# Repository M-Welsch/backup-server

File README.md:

# Backup Server (BaSe)

Your Home NAS requires you to make backups from time to time. Since you have better things to do, these will likely get forgotten or done irregulary. The Backup-Server aims on helping you out. It backs up your data on schedule and undocks the backup medium when the backup is done. This offers an unique way of data protection.

## Introduction (longer)

Like many other people (*cough* nerds) I have a home NAS that serves nextcloud and some other funny stuff. Thanks to a terrific community it became quite easy to setup such a thing. Many, many thanks to you all!
However, hosting my own server came with a serious disadvantage. I had to take care of the backups myself.

I built Backup Server to overcome this issue. It sleeps and therefore consumes very, very little current most of the times, wakes up when a backup is scheduled, docks to a hard drive, copys all the data from the nas, undocks and goes back to sleep.

## Implementation

The current verion is built around a banana pi mk1. It connects to the hard drive via a motor-driven pluggable sata-connection, which is the core of the whole thing. This way, the harddrive is only connected to anything if needed.

```mermaid
graph LR
A(Power Up)-->B(Dock external HDD)-->C(Conduct Backup)-->D(Schedule Next Backup)-->E(Undock external HDD)-->F(Schedule next Backup)-->G(Power Down)
```

## Outlook

the next hardware version shall be more flexible compared to our custom fit to the banana pi.

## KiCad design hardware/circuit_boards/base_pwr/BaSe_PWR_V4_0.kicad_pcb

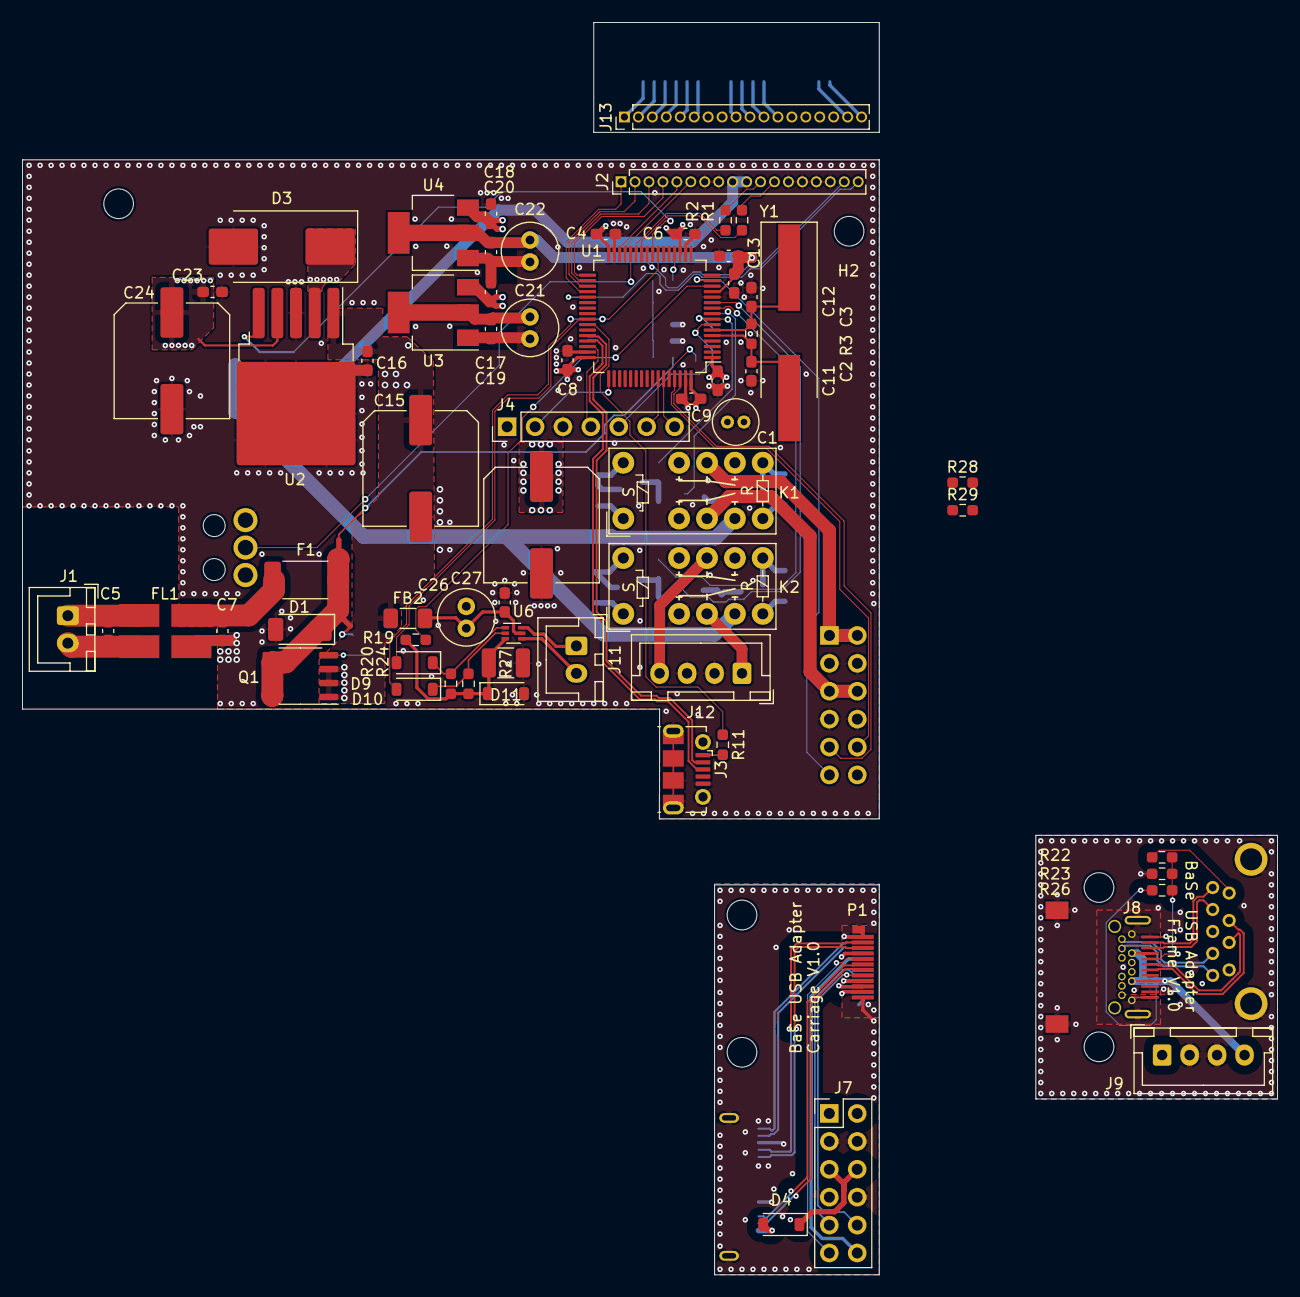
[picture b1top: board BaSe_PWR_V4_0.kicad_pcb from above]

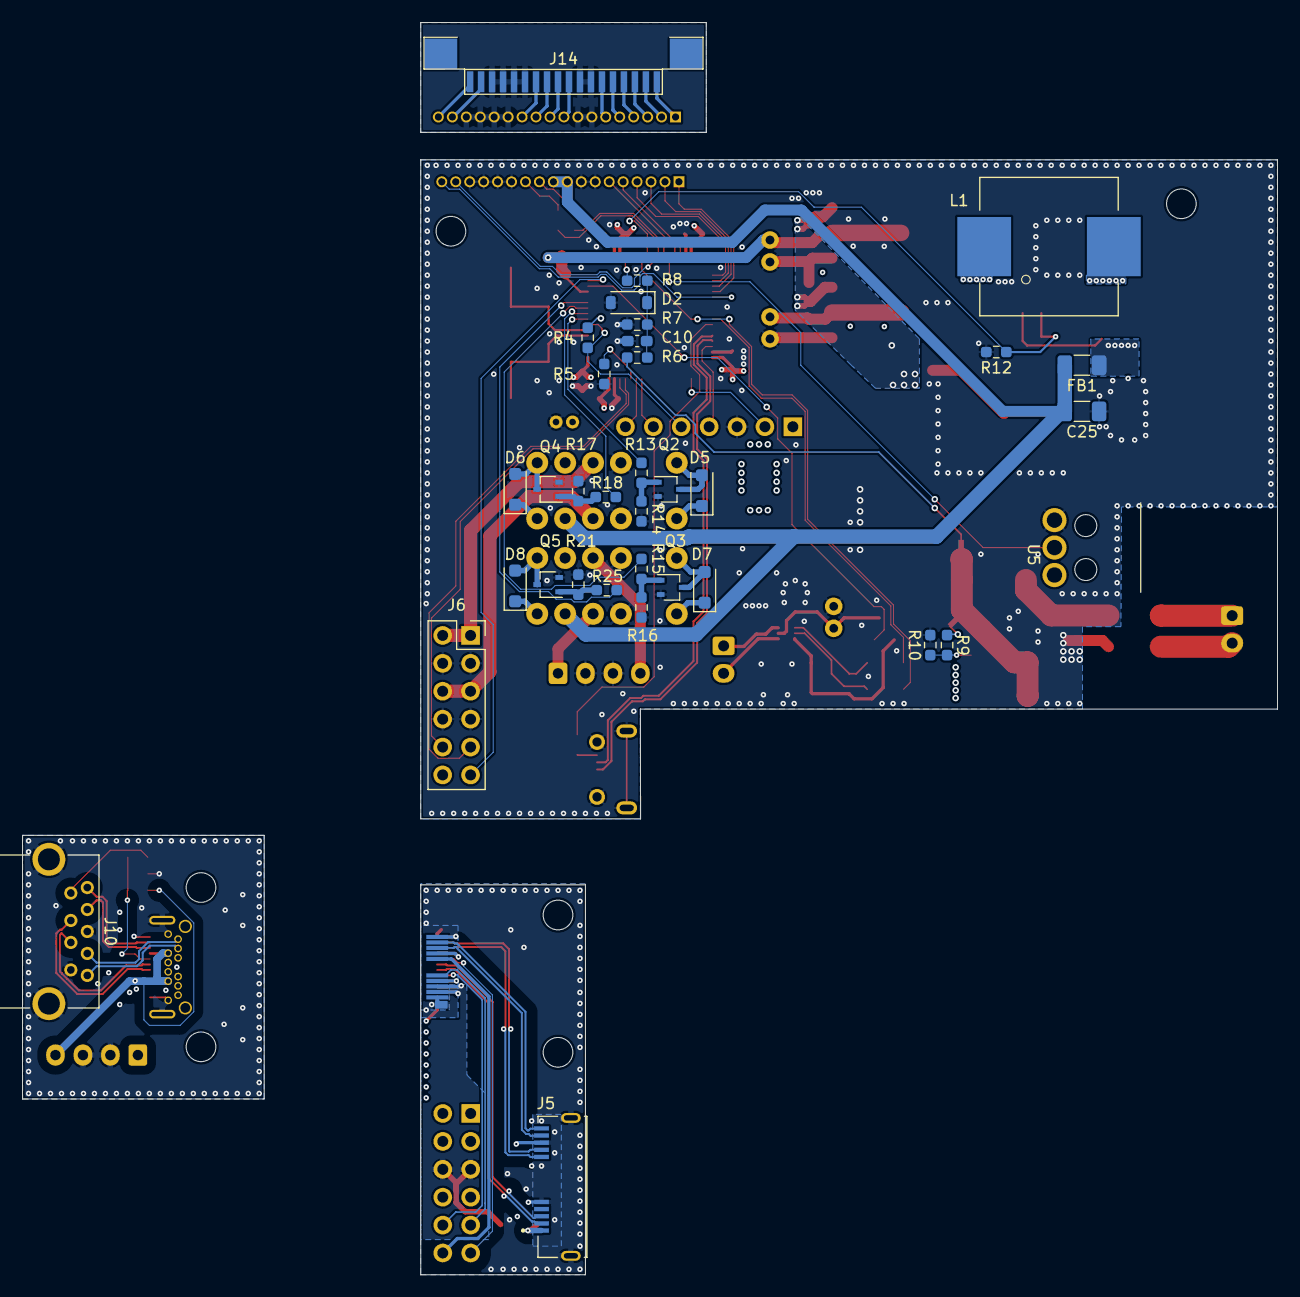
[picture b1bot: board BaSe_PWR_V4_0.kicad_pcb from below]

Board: 4 copper layers, 114.2 x 114.0 mm, 109 parts (34 on the bottom side), 106 nets.

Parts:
C1: 4.7µF; C_Radial_D4.0mm_H7.0mm_P1.50mm
C2, C3: 20pF; C_0603_1608Metric_Pad1.08x0.95mm_HandSolder
C4, C6, C8, C9, C10, C11, C16, C17, C18, C19, C20, C23, C27: 100nF; C_0603_1608Metric_Pad1.08x0.95mm_HandSolder
C5, C7: C_0603_1608Metric_Pad1.08x0.95mm_HandSolder
C12: 10nF; C_0603_1608Metric_Pad1.08x0.95mm_HandSolder
C13: 1µF; C_0603_1608Metric_Pad1.08x0.95mm_HandSolder
C14, C15, C24: 220µF; C_Elec_10x10.2
C21, C22, C26: 22µF; C_Radial_D5.0mm_H11.0mm_P2.00mm
C25: 10µF; C_1206_3216Metric_Pad1.33x1.80mm_HandSolder
D1: 824501121; D_SOD-128
D2, D9, D10: SD103CW-E3-08; D_SOD-123
D3: SK34-TP; D_SMC_Handsoldering
D4: SK64L-TPMSCT-ND; D_SOD-123
D5, D6, D7, D8: 1N4148WRHGCT-ND; D_SOD-123F
D11: 2.5V; D_SOD-123
F1: Fuse_2512_6332Metric_Pad1.52x3.35mm_HandSolder
FB1, FB2: FerriteBead; C_1206_3216Metric_Pad1.33x1.80mm_HandSolder
FL1: CMC_Laird_CM2021Y330R-10
H1, H2, H3, H4, H5, H6: MountingHole; MountingHole_2.7mm_M2.5_DIN965
J1: 12VDC In; JST_XH_B2B-XH-A_1x02_P2.50mm_Vertical
J2: HRS-1B-16-GA; PinHeader_1x18_P1.27mm_Vertical
J3: USB_B_Micro; USB_Micro-B_Molex-105017-0001
J4: Conn_01x07_Pin; PinHeader_1x07_P2.54mm_Vertical
J5: USB3_B_Micro; conn_usb3bmicro_GSB343K331HR
J6: Conn_02x06_Odd_Even; PinSocket_2x06_P2.54mm_Vertical
J7: Conn_02x06_Odd_Even; PinHeader_2x06_P2.54mm_Vertical
J8: USB_C_Receptacle; conn_usbc_socket_RAHPCUC31AU1TR
J9, J12: Conn_01x04_Socket; JST_XH_B4B-XH-A_1x04_P2.50mm_Vertical
J10: USB3_A; STEWARD_USB3_A_SS-52000-001
J11: MOTOR; JST_XH_B2B-XH-A_1x02_P2.50mm_Vertical
J13: HPH1-A-16-UA; PinHeader_1x18_P1.27mm_Vertical
J14: molex_fcc_05220
K1, K2: Kemet_EC2-12TNU
L1: 47µH; L_Wuerth_WE-PD-Typ-LS_Handsoldering
NT1, NT2: NetTie_2; NetTie-2_SMD_Pad0.5mm
P1: USB_C_Plug; Molex_USBC_Plug_1054440011
Q1: AOSP21321; SO-8_3.9x4.9mm_P1.27mm
Q2, Q3, Q4, Q5: BSS214NW; SOT-323_SC-70
R1, R2, R8, R10: 100; R_0603_1608Metric_Pad0.98x0.95mm_HandSolder
R3: R; R_0603_1608Metric_Pad0.98x0.95mm_HandSolder
R4, R5, R11, R20, R24, R28: 10k; R_0603_1608Metric_Pad0.98x0.95mm_HandSolder
R6, R9: 100k; R_0603_1608Metric_Pad0.98x0.95mm_HandSolder
R7: 24,9k; R_0603_1608Metric_Pad0.98x0.95mm_HandSolder
R12, R14, R16, R17, R21: 47k; R_0603_1608Metric_Pad0.98x0.95mm_HandSolder
R13, R15, R18, R19, R25: 1k; R_0603_1608Metric_Pad0.98x0.95mm_HandSolder
R22: 13,3k; R_0603_1608Metric_Pad0.98x0.95mm_HandSolder
R23: 3,16k; R_0603_1608Metric_Pad0.98x0.95mm_HandSolder
R26: 15,8k; R_0603_1608Metric_Pad0.98x0.95mm_HandSolder
R27: R; R_1210_3225Metric_Pad1.30x2.65mm_HandSolder
R29: 8,87k; R_0603_1608Metric_Pad0.98x0.95mm_HandSolder
U1: STM32F070RBTx; LQFP-64_10x10mm_P0.5mm
U2: LM2596S-5; TO-263-5_TabPin3
U3, U4: AMS1117-3.3; SOT-223-3_TabPin2
U5: TS0101F020V4
U6: DRV8220; SOT-563
Y1: 8MHz; Crystal_SMD_HC49-SD_HandSoldering

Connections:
+3.3VA: C12.1, C13.1, C20.1, C22.1, U1.13 (VDDA), U4.2 (VO)
+3V3_STBY: C1.1, C4.1, C6.1, C8.1, C9.1, C11.1, C19.1, C21.1, J4.1, J6.12, R4.2, R28.1, R29.2, U1.1 (VDD), U1.19 (VDD), U1.32 (VDD), U1.48 (VDD), U1.64 (VDD), U3.2 (VO)
+5V: C25.2, FB1.2, J2.9, J2.10, K1.5, K2.5
+5VA: J8.A10 (RX2-), J8.A11 (RX2+), J8.B2 (TX2+), J8.B3 (TX2-), J9.1, J10.1 (VBUS), R22.1
+12V: C14.1, C15.1, C16.2, C17.1, C18.1, D5.1 (K), D6.1 (K), D7.1 (K), D8.1 (K), FB2.1, K1.1, K1.6, K1.8, K2.1, K2.6, K2.8, Q1.1 (S), Q1.2 (S), Q1.3 (S), U2.1 (VIN), U3.3 (VI), U4.3 (VI)
+12VA: J8.A4 (VBUS), J8.A9 (VBUS), J8.B4 (VBUS), J8.B9 (VBUS), J9.4, R26.1
/12v_motor: C26.1, C27.1, FB2.2, U6.5 (VM)
/12vin_meas: R8.2, U1.20 (PA4)
/+5V_HDD: J6.5, J6.6, K1.4
/+5V_HDD_: D4.1 (K), J7.5, J7.6, P1.A10 (RX2-), P1.A11 (RX2+), P1.B2 (TX2+), P1.B3 (TX2-)
/+5V_sbu: J12.1, K2.4
/+5v_out: C23.2, C24.1, FB1.1, L1.2, U2.4 (FB)
/+12V_HDD: J6.1, J6.2, K1.9
/+12V_HDD_: J7.1, J7.2, P1.A4 (VBUS), P1.A9 (VBUS), P1.B4 (VBUS), P1.B9 (VBUS)
/+12V_sbu: J12.4, K2.9
/DC_IN+: C5.2, FL1.1, J1.1
/DC_IN-: C5.1, FL1.2, J1.2
/DC_prefuse: C7.1, F1.2, FL1.4
/DC_preprot: D1.1 (A1), F1.1, NT1.2, NT2.2, Q1.5 (D), Q1.6 (D), Q1.7 (D), Q1.8 (D)
/Dis_DB4: J2.4, U1.33 (PB12)
/Dis_DB5: J2.3, U1.34 (PB13)
/Dis_DB6: J2.2, U1.35 (PB14)
/Dis_DB7: J2.1, U1.36 (PB15)
/Dis_E: J2.5, U1.30 (PB11)
/Dis_PWM: J2.12, R1.2
/Dis_RS: J2.6, U1.29 (PB10)
/GND_HMI: J13.7, J13.8, J13.13, J13.14, J13.15, J13.16, J14.7, J14.8, J14.13, J14.14, J14.15, J14.16
/LED_HMI: J2.11, R2.2
/SW: D3.1 (K), L1.1, U2.2 (OUT)
/SW_HDD_Off: R18.1, U1.9 (PC1)
/SW_HDD_On: R13.1, U1.8 (PC0)
/Taster_0: J2.17, U1.25 (PC5)
/Taster_1: J2.18, U1.37 (PC6)
/USB_D+: J3.3 (D+), U1.45 (PA12)
/USB_D-: J3.2 (D-), U1.44 (PA11)
/aux_3v3: J7.12, P1.B8 (SBU2)
/aux_i2c_scl: J7.10, P1.A8 (SBU1)
/aux_i2c_sda: J7.9, P1.B5 (VCONN)
/boot0: R5.1, U1.60 (BOOT0)
/hmi_pwm0: R1.1, U1.26 (PB0)
/hmi_pwm1: R2.1, U1.27 (PB1)
/i2c1_scl: J6.10, U1.61 (PB8)
/i2c1_sda: J6.9, U1.62 (PB9)
/imotor: D11.1 (K), R19.2, R20.2, R24.2, R27.1, U6.3 (GND)
/imotor_prot: R19.1, U1.14 (PA0)
/in1: D9.1 (K), R20.1, U6.1 (IN1)
/in1_mcu: D9.2 (A), U1.41 (PA8)
/in2: D10.1 (K), R24.1, U6.2 (IN2)
/in2_mcu: D10.2 (A), U1.23 (PA7)
/l1_rx+: J8.B11 (RX1+), J10.6 (SSRX+)
/l1_rx-: J8.B10 (RX1-), J10.5 (SSRX-)
/l1_tx+: J8.A2 (TX1+), J10.9 (SSTX+)
/l1_tx-: J8.A3 (TX1-), J10.8 (SSTX-)
/lane1_d+: J8.A6 (D+), J10.3 (D+)
/lane1_d-: J8.A7 (D-), J10.2 (D-)
/motor1: J11.1, U6.6 (OUT1)
/motor2: J11.2, U6.4 (OUT2)
/stator_d+: J5.3 (D+), P1.A6 (D+)
/stator_d-: J5.2 (D-), P1.A7 (D-)
/stator_rx+: J5.10 (SSRX+), P1.B11 (RX1+)
/stator_rx-: J5.9 (SSRX-), P1.B10 (RX1-)
/stator_supply_sense: J6.11, R29.1, U1.15 (PA1)
/stator_supply_sense_: J7.11, P1.A5 (CC), R28.2
/stator_tx+: J5.7 (SSTX+), P1.A2 (TX1+)
/stator_tx-: J5.6 (SSTX-), P1.A3 (TX1-)
/supply_sense: J8.A5 (CC1), R22.2, R23.1, R26.2
/sw_sbu_off: R25.1, U1.11 (PC3)
/sw_sbu_on: R15.1, U1.10 (PC2)
/swclk: J4.2, U1.49 (PA14)
/swdio: J4.4, U1.46 (PA13)
/usart1_rx: J4.7, U1.59 (PB7)
/usart1_tx: J4.6, U1.58 (PB6)
/vbus_sense: R11.1, U1.42 (PA9)
/~LM2596S_ON: R12.1, U1.24 (PC4), U2.5 (~ON/OFF)
/~endswitch_undocked: U1.28 (PB2), U5.NO
/~rst: J4.5, R4.1, U1.7 (NRST)
GND: C1.2, C2.1, C3.1, C4.2, C6.2, C7.2, C8.2, C9.2, C10.2, C11.2, C12.2, C13.2, C14.2, C15.2, C16.1, C17.2, C18.2, C19.2, C20.2, C21.2, C22.2, C23.1, C24.2, C25.1, C26.2, C27.2, D1.2 (A2), D2.2 (A), D3.2 (A), D11.2 (A), FL1.3, J2.7, J2.8, J2.13, J2.14, J2.15, J2.16, J3.5 (GND), J3.6 (Shield), J4.3, J6.3, J6.4, J6.7, J6.8, J12.2, J12.3, K1.3, K1.10, K2.3, K2.10, Q2.2 (S), Q3.2 (S), Q4.2 (S), Q5.2 (S), R5.2, R7.1, R10.2, R12.2, R14.1, R16.1, R17.1, R21.1, R27.2, U1.12 (VSSA), U1.18 (VSS), U1.31 (VSS), U1.47 (VSS), U1.63 (VSS), U2.3 (GND), U3.1 (GND), U4.1 (GND), U5.C
GND1: J5.5 (GND), J5.8 (DRAIN), J5.11 (SHIELD), J7.3, J7.4, J7.7, J7.8, P1.A1 (GND), P1.A12 (GND), P1.B1 (GND), P1.B12 (GND), P1.S1 (SHIELD)
GND2: J8.A1 (GND), J8.A12 (GND), J8.B1 (GND), J8.B12 (GND), J8.S1 (SHIELD), J9.2, J9.3, J10.4 (GND), J10.7 (DRAIN), J10.10 (SHIELD), R23.2
unnamed: C10.1, D2.1 (K), R6.1, R7.2, R8.1
unnamed: D4.2 (A), J5.1 (VBUS)
unnamed: D5.2 (A), K1.12, Q2.3 (D)
unnamed: D6.2 (A), K1.7, Q4.3 (D)
unnamed: D7.2 (A), K2.12, Q3.3 (D)
unnamed: D8.2 (A), K2.7, Q5.3 (D)
unnamed: J3.1 (VBUS), R11.2
unnamed: J13.1, J14.1
unnamed: J13.2, J14.2
unnamed: J13.3, J14.3
unnamed: J13.4, J14.4
unnamed: J13.5, J14.5
unnamed: J13.6, J14.6
unnamed: J13.9, J13.10, J14.9, J14.10
unnamed: J13.11, J14.11
unnamed: J13.12, J14.12
unnamed: J13.17, J14.17
unnamed: J13.18, J14.18
unnamed: NT1.1, R6.2
unnamed: NT2.1, R9.1
unnamed: Q1.4 (G), R9.2, R10.1
unnamed: Q2.1 (G), R13.2, R14.2
unnamed: Q3.1 (G), R15.2, R16.2
unnamed: Q4.1 (G), R17.2, R18.2
unnamed: Q5.1 (G), R21.2, R25.2
unnamed: C2.2, R3.1, U1.5 (PF0), Y1.2
unnamed: C3.2, R3.2, U1.6 (PF1), Y1.1

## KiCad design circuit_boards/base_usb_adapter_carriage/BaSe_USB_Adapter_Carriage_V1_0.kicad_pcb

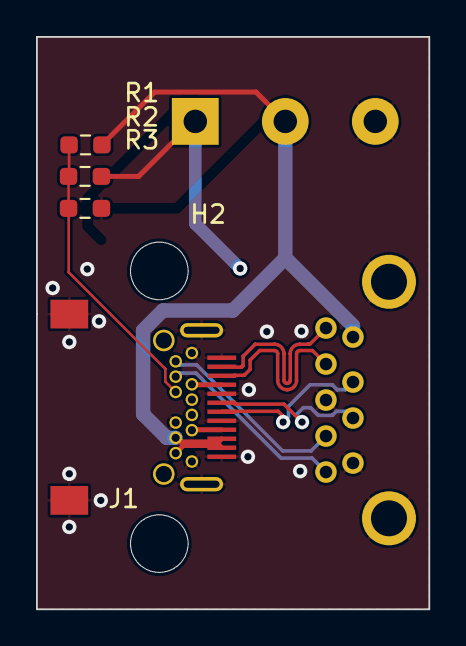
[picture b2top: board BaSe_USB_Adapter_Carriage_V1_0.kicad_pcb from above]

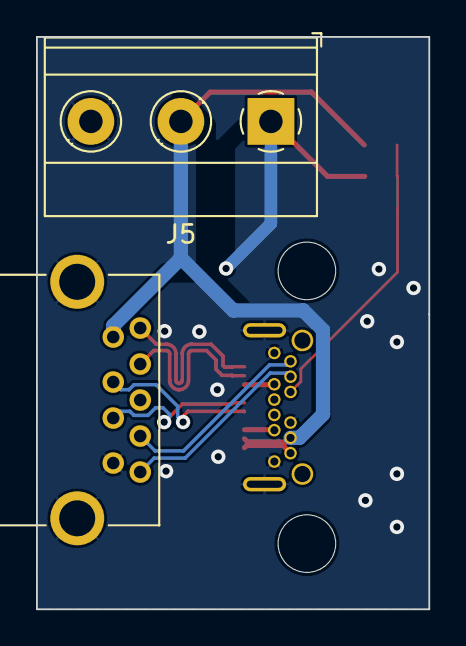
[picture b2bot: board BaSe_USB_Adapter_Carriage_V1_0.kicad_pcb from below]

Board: 4 copper layers, 21.8 x 31.8 mm, 8 parts (2 on the bottom side), 10 nets.

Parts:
H1, H2: MountingHole; MountingHole_3.2mm_M3_DIN965
J1: USB_C_Receptacle; conn_usbc_socket_RAHPCUC31AU1TR
J3: USB3_A; STEWARD_USB3_A_SS-52000-001
J5: Screw_Terminal_01x03; TerminalBlock_Phoenix_MKDS-1,5-3_1x03_P5.00mm_Horizontal
R1: 31k6; R_0603_1608Metric_Pad0.98x0.95mm_HandSolder
R2: 38k3; R_0603_1608Metric_Pad0.98x0.95mm_HandSolder
R3: 10k; R_0603_1608Metric_Pad0.98x0.95mm_HandSolder

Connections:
+5V: J1.A10 (RX2-), J1.A11 (RX2+), J1.B2 (TX2+), J1.B3 (TX2-), J3.1 (VBUS), J5.2, R1.1
+12V: J1.A4 (VBUS), J1.A9 (VBUS), J1.B4 (VBUS), J1.B9 (VBUS), J5.1, R2.1
/l1_rx+: J1.B11 (RX1+), J3.6 (SSRX+)
/l1_rx-: J1.B10 (RX1-), J3.5 (SSRX-)
/l1_tx+: J1.A2 (TX1+), J3.9 (SSTX+)
/l1_tx-: J1.A3 (TX1-), J3.8 (SSTX-)
/lane1_d+: J1.A6 (D+), J3.3 (D+)
/lane1_d-: J1.A7 (D-), J3.2 (D-)
/supply_sense: J1.B8 (SBU2), R1.2, R2.2, R3.1
GND2: J1.A1 (GND), J1.A5 (CC1), J1.A8 (SBU1), J1.A12 (GND), J1.B1 (GND), J1.B5 (CC2), J1.B12 (GND), J1.S1 (SHIELD), J3.4 (GND), J3.7 (DRAIN), J3.10 (SHIELD), J5.3, R3.2

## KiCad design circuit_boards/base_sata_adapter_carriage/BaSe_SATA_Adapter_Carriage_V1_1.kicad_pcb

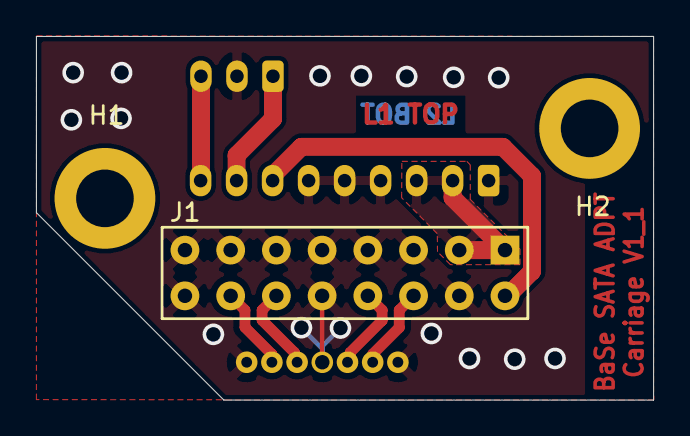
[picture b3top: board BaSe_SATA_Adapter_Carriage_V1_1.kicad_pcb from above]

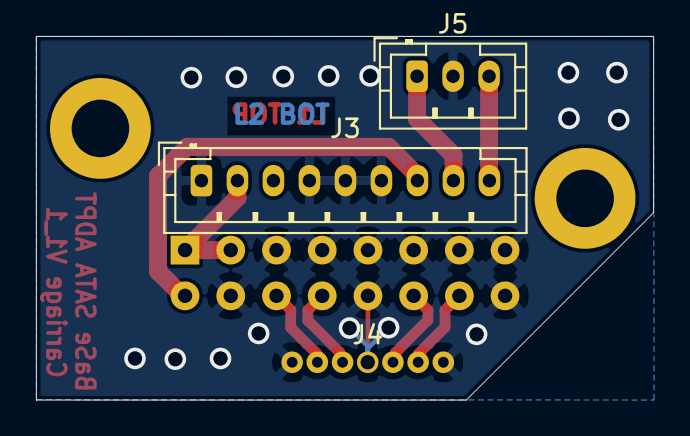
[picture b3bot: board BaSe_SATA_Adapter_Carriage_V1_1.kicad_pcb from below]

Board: 2 copper layers, 34.3 x 20.2 mm, 7 parts (3 on the bottom side), 9 nets.

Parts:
Cable_HDD_ENDSW_preconfected1: ASPHSPH24K305; BOM_ITEM
H1, H2: MountingHole_Pad; MountingHole_3.2mm_M3_DIN965_Pad
J1: 419-10-216-00-006000; Conn_Spring_Counterpart_MaxMill_823-22-016-10-0001101
J3: Conn_01x09; JST_PH_B9B-PH-K_1x09_P2.00mm_Vertical
J4: Conn_01x07_Female; SATA_Cable_Intake
J5: Conn_01x03; JST_PH_B3B-PH-K_1x03_P2.00mm_Vertical

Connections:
+5VA: J1.2, J3.7
+12VA: J1.1, J1.3, J3.2, J3.3
/Cable_Rx+: J1.6, J4.6
/Cable_Rx-: J1.8, J4.5
/Cable_Tx+: J1.14, J4.2
/Cable_Tx-: J1.12, J4.3
/~Endswitch_Docked: J3.8, J5.1
/~Endswitch_Undocked: J3.9, J5.3
GNDA: J1.4, J1.5, J1.7, J1.9, J1.10, J1.11, J1.13, J1.15, J1.16, J3.1, J3.4, J3.5, J3.6, J4.1, J4.4, J4.7, J5.2

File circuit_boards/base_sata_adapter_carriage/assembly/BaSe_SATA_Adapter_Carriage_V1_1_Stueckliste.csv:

Refs,Value,Footprint,Quantity,MFR,MPN,SPR,SPN
J5,Conn_01x03,Connector_JST:JST_PH_B3B-PH-K_1x03_P2.00mm_Vertical,1,JST Sales America Inc.,B3B-PH-K-S(LF)(SN),Digikey,455-1705-ND
J3,Conn_01x09,Connector_JST:JST_PH_B9B-PH-K_1x09_P2.00mm_Vertical,1,JST Sales America Inc.,-,Digikey,455-1711-ND
Cable_HDD_ENDSW_preconfected1,ASPHSPH24K305,G7_Custom:BOM_ITEM,1,JST Sales America Inc.,-,Digikey,455-3083-ND
J1,419-10-216-00-006000,G7_Custom:Conn_Spring_Counterpart_MaxMill_823-22-016-10-0001101,1,Mill-Max Manufacturing Corp.,419-10-216-00-006000,Digikey, ED1379-ND
J4,Conn_01x07_Female,G7_Custom:SATA_Cable_Intake,1,-,-,-,-
PCB1,BaSe_SATA_Adapter_Carriage_V1_1,G7_Labels:BaSe_SATA_Adapter_Carriage_V1_1,1,-,-,-,-
H1;H2,MountingHole_Pad,MountingHole:MountingHole_3.2mm_M3_DIN965_Pad,2,-,-,-,-

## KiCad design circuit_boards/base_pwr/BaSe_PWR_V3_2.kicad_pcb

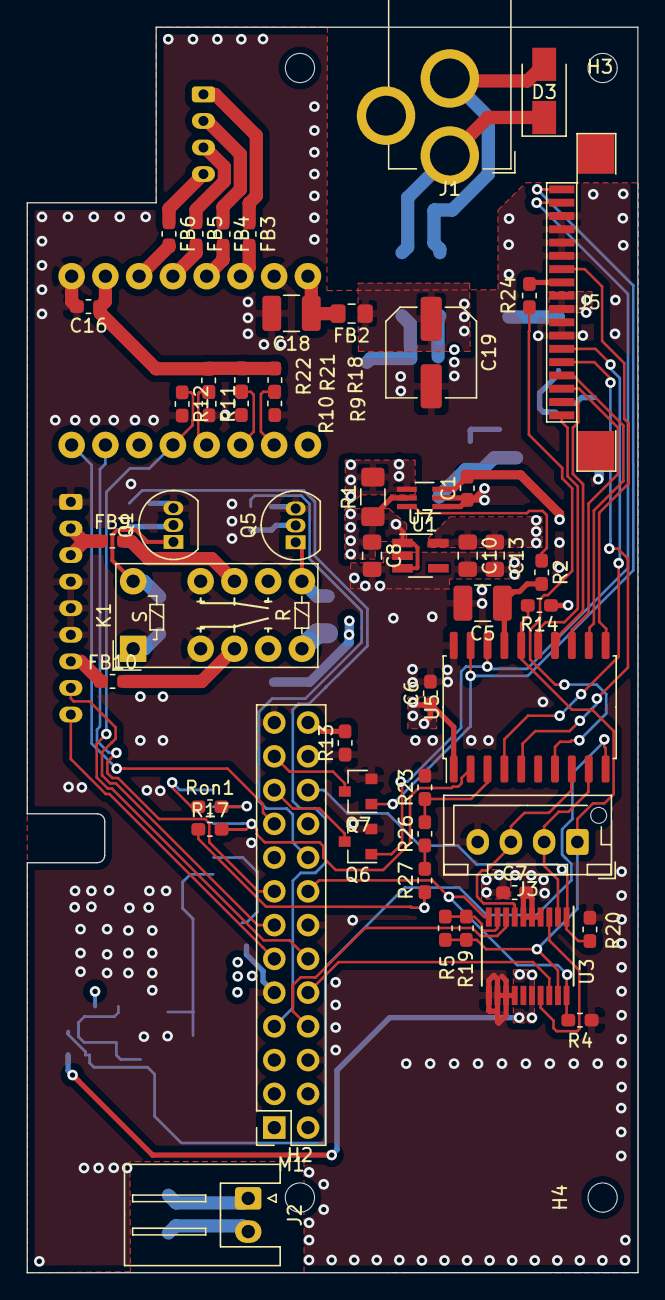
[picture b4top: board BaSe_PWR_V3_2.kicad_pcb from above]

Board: 4 copper layers, 46.0 x 93.7 mm, 110 parts (0 on the bottom side), 78 nets.

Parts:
2k3: 47k; R_0603_1608Metric_Pad1.05x0.95mm_HandSolder
2k4: 1k2; R_0603_1608Metric_Pad1.05x0.95mm_HandSolder
C1, C6, C7, C16: 100nF; C_0603_1608Metric_Pad1.05x0.95mm_HandSolder
C2, C3, C8, C10, C13, C17, C20: 1µF; C_0805_2012Metric_Pad1.15x1.40mm_HandSolder
C4, C11: 100µF; C_1210_3225Metric_Pad1.42x2.65mm_HandSolder
C5, C15, C18: 10µF; C_1210_3225Metric_Pad1.42x2.65mm_HandSolder
C9: 10nF; C_0603_1608Metric_Pad1.05x0.95mm_HandSolder
C12: 47nF; C_1210_3225Metric_Pad1.42x2.65mm_HandSolder
C14, C19: 220µF; C_Elec_6.3x7.7
C24: 1nF; C_0603_1608Metric_Pad1.05x0.95mm_HandSolder
Cable_BPi_SPLY_preconfected1, Cable_BPi_SPLY_preconfected2: ASXHSXH22K51; BOM_ITEM
Cable_HDD_ENDSW_preconfected2: ASPHSPH24K152; BOM_ITEM
Cable_Stepper_preconfected1, Cable_Stepper_preconfected2, Cable_Stepper_preconfected3, Cable_Stepper_preconfected4: ASPHSPH24K51‎; BOM_ITEM
Conn_Socket_BPi_SPLY1: XHP-2; BOM_ITEM
Conn_Socket_BPi_SPLY_atJ5: XHP-2; BOM_ITEM
Conn_Socket_PWR_HDD1: PHR-9; BOM_ITEM
Conn_Socket_Stepper1: PHR-4; BOM_ITEM
Conn_Socket_at_Stepper1: PHR-6; BOM_ITEM
D1, D2: 1N4148; D_SOD-123F
D3: 824501121; D_SMA
D4, D5: NO; D_SMA
D6: NO; D_SMC
F1: Fuse; Fuse_Littelfuse-NANO2-451_453
FB2: 742792093; L_0805_2012Metric_Pad1.15x1.40mm_HandSolder
FB3, FB4, FB5, FB6, FB7, FB10: 742792602; L_0603_1608Metric_Pad1.05x0.95mm_HandSolder
FB9: 0R; R_0603_1608Metric_Pad1.05x0.95mm_HandSolder
FFC_Cable1: 0151670333; BOM_ITEM
FL1, FL2: CM2021Y330R-10; CMC_Laird_CM2021Y330R-10
H1, H2, H3, H4: MountingHole; MountingHole_2.2mm_M2
J1: 12V Power In; BarrelJack_Wuerth_6941xx301002
J2: BPi Supply; JST_XH_S2B-XH-A_1x02_P2.50mm_Horizontal
J3: DebugAtTiny; JST_XH_B4B-XH-AM_1x04_P2.50mm_Vertical
J4: B9B-PH-K-S(LF)(SN); JST_PH_B9B-PH-K_1x09_P2.00mm_Vertical
J5: Molex 0522071860; Conn_FFC_Molex_52207-1860
J6: B4B-PH-K-S(LF)(SN); JST_PH_B4B-PH-K_1x04_P2.00mm_Vertical
K1: EC2-12TNU; Relay_Kemet_EC2-12TNU
M1: BananaPi_M1; BananaPi-M1
PCB1: BaSe_PWR_V3_2
Q1, Q5: BS170; TO-92_Inline
Q2, Q6, Q7: BSS123; SOT-23
Q3: BSC028N06LS3; TDSON-8-1
Q4: BSC093N04LS; TDSON-8-1
R1: 1m; R_1206_3216Metric_Pad1.42x1.75mm_HandSolder
R2, R4, R8, R9, R10, R11, R14, R15, R16, R17, R20, R25: 47k; R_0603_1608Metric_Pad1.05x0.95mm_HandSolder
R3: 1k; R_0603_1608Metric_Pad1.05x0.95mm_HandSolder
R5, R19: 10k; R_0603_1608Metric_Pad1.05x0.95mm_HandSolder
R6, R24: 1k2; R_0603_1608Metric_Pad1.05x0.95mm_HandSolder
R7, R18, R21, R22, R26, R27: NO; R_0603_1608Metric_Pad1.05x0.95mm_HandSolder
R12: 100k; R_0603_1608Metric_Pad1.05x0.95mm_HandSolder
R13, R23: 0; R_0603_1608Metric_Pad1.05x0.95mm_HandSolder
Rfbb1: 1,87K; R_0603_1608Metric_Pad1.05x0.95mm_HandSolder
Rfbt1: 10k; R_0603_1608Metric_Pad1.05x0.95mm_HandSolder
Ron1: 47k; R_0603_1608Metric_Pad1.05x0.95mm_HandSolder
SCT1: A4988_Module
U1: INA212; SOT-363_SC-70-6_Handsoldering
U2: LMZ12003; LMZ12003_Handsolder
U3: ADG734; TSSOP-20_4.4x6.5mm_P0.65mm
U4: LTC4359-MS8; MSOP-8_3x3mm_P0.65mm_Py0.45mm
U5: ATtiny816-S; SOIC-20W_7.5x12.8mm_P1.27mm
U7: AP2204K-3.3; SOT-23-5_HandSoldering

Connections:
+3V3: C16.1, M1.1, R18.1, R21.1, R22.1, SCT1.10
+3V3_STBY: C1.2, C6.1, C7.1, C10.1, C13.1, R7.2, R14.1, R17.1, R27.1, U1.3, U3.16, U5.1, U7.5
+5V: C4.1, C11.1, C24.1, J5.9, J5.10, K1.5, Q4.5, Rfbt1.1, U2.7
+12V: C8.1, C19.1, D1.1, D2.1, FB2.1, FB7.2, K1.1, K1.6, K1.8, R1.1, R16.1, U1.5, U7.1, U7.3
/5V_EN: R17.2, U2.3, U5.2
/5V_Ron: Ron1.2, U2.2
/12V_Prot: C12.1, C15.1, D6.1, Q3.5, R1.2, U1.4, U4.8
/12V_nProt: D4.1, D6.2, F1.1, Q3.1, Q3.2, Q3.3, R15.1, U4.2, U4.4
/+5V_HDD: FB10.2, K1.4
/+5V_HDD_flt: FB10.1, J4.7
/+12V_HDD: FB9.2, K1.9
/+12V_HDD_flt: FB9.1, J4.2, J4.3
/DC_IN+: C2.2, D3.1, FL1.1, J1.1
/DC_IN-: C2.1, D3.2, FL1.2, J1.2
/DIS_BPi_SPLY: Q2.1, R7.1, R25.2, U5.10
/Dis_DB4: J5.4, U5.12
/Dis_DB5: J5.3, U5.13
/Dis_DB6: J5.2, U5.14
/Dis_DB7: J5.1, U5.15
/Dis_E: J5.5, U5.5
/Dis_PWM: J5.12, U5.11
/Dis_RS: J5.6, U5.4
/EN_attiny_link: M1.22, R20.1, U3.1
/LED_HMI: J5.11, R24.2
/LED_HMI_attiny: R24.1, U5.7
/MS1: R9.1, R18.2, SCT1.2
/MS2: R10.1, R21.2, SCT1.3
/MS3: R11.1, R22.2, SCT1.4
/RxD_BPi: M1.10, U3.18
/RxD_attiny: J3.3, U3.7, U5.8
/SW_HDD_Off: 2k4.1, M1.18
/SW_HDD_On: M1.7, R6.1
/Step_1A: FB5.2, SCT1.12
/Step_1B: FB6.2, SCT1.11
/Step_2A: FB4.2, SCT1.13
/Step_2B: FB3.2, SCT1.14
/Stepper_Dir: M1.19, SCT1.8
/Stepper_Step: M1.15, SCT1.7
/Stepper_~Reset: M1.12, R12.1, SCT1.5
/Taster_0: J5.17, Q6.1, U5.18
/Taster_1: J5.18, Q7.1, U5.19
/TxD_BPi: M1.8, U3.8
/TxD_attiny: J3.2, U3.2, U5.9
/TxD_attiny_prot: U3.3, U3.17
/V_meas: R2.1, U1.6
/V_meas_flt: C5.1, R2.2, U5.17
/Version: R23.1, R26.2, U5.3
/Vin_Buck: C14.1, FB7.1, Ron1.1, U2.1
/Vin_Stepper: C18.1, FB2.2, SCT1.16
/attiny_program_~communicate: M1.16, R4.1, U3.10, U3.20
/attiny_~reset: J3.1, R5.1, R14.2, R19.1, U3.19, U5.16
/rev2_~rev3: M1.26, R13.2
/~Endswitch_Docked: J4.8, M1.13
/~Endswitch_Undocked: J4.9, M1.11
/~Taster_0: M1.21, Q6.3
/~Taster_1: M1.23, Q7.3
GND: 2k3.1, C1.1, C3.2, C4.2, C5.2, C6.2, C7.2, C8.2, C9.2, C10.2, C11.2, C13.2, C14.2, C15.2, C16.2, C17.2, C18.2, C19.2, FL1.3, FL2.4, J3.4, J4.1, J4.4, J4.5, J4.6, J5.7, J5.8, J5.13, J5.14, J5.15, J5.16, K1.3, K1.10, M1.6, M1.9, M1.14, M1.20, M1.25, Q1.3, Q2.2, Q5.3, Q6.2, Q7.2, R3.2, R4.2, R8.1, R9.2, R10.2, R11.2, R12.2, R13.1, R20.2, R23.2, R25.1, Rfbb1.2, SCT1.9, SCT1.15, U1.1, U1.2, U2.4, U2.8, U3.4, U3.5, U3.6, U3.11, U3.12, U3.13, U3.14, U5.20, U7.2
unnamed: 2k3.2, 2k4.2, Q5.2
unnamed: C3.1, F1.2, FL1.4
unnamed: C9.1, U2.5
unnamed: C12.2, D5.1, R3.1, U4.6
unnamed: C17.1, FL2.3, Q4.1, Q4.2, Q4.3
unnamed: C20.1, FL2.2, J2.2
unnamed: C20.2, FL2.1, J2.1
unnamed: C24.2, Rfbb1.1, Rfbt1.2, U2.6
unnamed: D1.2, K1.12, Q1.1
unnamed: D2.2, K1.7, Q5.1
unnamed: D4.2, D5.2
unnamed: FB3.1, J6.1
unnamed: FB4.1, J6.2
unnamed: FB5.1, J6.3
unnamed: FB6.1, J6.4
unnamed: Q1.2, R6.2, R8.2
unnamed: Q2.3, Q4.4, R16.2
unnamed: Q3.4, U4.1
unnamed: R15.2, U4.5
unnamed: R5.2, R19.2, U3.9
unnamed: R26.1, R27.2

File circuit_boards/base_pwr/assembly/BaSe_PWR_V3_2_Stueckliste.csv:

Refs,Value,Footprint,Quantity,MFR,MPN,SPR,SPN
C1;C16;C6;C7,100nF,Capacitor_SMD:C_0603_1608Metric_Pad1.05x0.95mm_HandSolder,4,-,-,-,399-7845-1-ND 
C9,10nF,Capacitor_SMD:C_0603_1608Metric_Pad1.05x0.95mm_HandSolder,1,-,-,-, 311-1572-1-ND
C24,1nF,Capacitor_SMD:C_0603_1608Metric_Pad1.05x0.95mm_HandSolder,1,-,-,-,311-1080-1-ND
C2;C3;C10;C8;C13;C20;C17,1µF,Capacitor_SMD:C_0805_2012Metric_Pad1.15x1.40mm_HandSolder,7,-,-,Digikey,732-7672-1-ND 
C11;C4,100µF,Capacitor_SMD:C_1210_3225Metric_Pad1.42x2.65mm_HandSolder,2,-,-,-, 587-1387-1-ND
C5;C18;C15,10µF,Capacitor_SMD:C_1210_3225Metric_Pad1.42x2.65mm_HandSolder,3,-,-,-,1276-1150-1-ND
C12,47nF,Capacitor_SMD:C_1210_3225Metric_Pad1.42x2.65mm_HandSolder,1,-,-,Digikey,1276-1150-1-ND
C19;C14,220µF,Capacitor_SMD:C_Elec_6.3x7.7,2,-,-,-,PCE4537CT-ND 
J6,B4B-PH-K-S(LF)(SN),Connector_JST:JST_PH_B4B-PH-K_1x04_P2.00mm_Vertical,1,JST Sales America Inc.,B4B-PH-K-S(LF)(SN),Digikey,455-1706-ND
J4,B9B-PH-K-S(LF)(SN),Connector_JST:JST_PH_B9B-PH-K_1x09_P2.00mm_Vertical,1,JST Sales America Inc.,-,Digikey,455-1711-ND
J2,BPi Supply,Connector_JST:JST_XH_S2B-XH-A_1x02_P2.50mm_Horizontal,1,JST,-,Digikey,455-2257-ND
D3,824501121,Diode_SMD:D_SMA,1,-,-,Digikey, 732-9949-1-ND
D4;D5,NO,Diode_SMD:D_SMA,2,-,-,-,-
D6,NO,Diode_SMD:D_SMC,1,-,-,-,SK64L-TPMSCT-ND
D2;D1,1N4148,Diode_SMD:D_SOD-123F,2,-,-,-,1N4148WRHGCT-ND 
F1,Fuse,Fuse:Fuse_Littelfuse-NANO2-451_453,1,-,-,-,F3147CT-ND 
SCT1,A4988_Module,G7_Custom:A4988_Module,1,-,-,-,-
FFC_Cable1,0151670333,G7_Custom:BOM_ITEM,1,-,0151670333,Digikey,WM16429-ND
Cable_HDD_ENDSW_preconfected2,ASPHSPH24K152,G7_Custom:BOM_ITEM,1,-,ASPHSPH24K152,Digikey,455-3082-ND
Cable_Stepper_preconfected1;Cable_Stepper_preconfected2;Cable_Stepper_preconfected3;Cable_Stepper_preconfected4,ASPHSPH24K51‎ ,G7_Custom:BOM_ITEM,4,-,-,Digikey,‎455-3081-ND‎
Cable_BPi_SPLY_preconfected2;Cable_BPi_SPLY_preconfected1,ASXHSXH22K51,G7_Custom:BOM_ITEM,2,-,-,Digikey,455-3239-ND
Conn_Socket_Stepper1,PHR-4,G7_Custom:BOM_ITEM,1,-,-,Digikey,455-1164-ND
Conn_Socket_at_Stepper1,PHR-6,G7_Custom:BOM_ITEM,1,-,-,Digikey, 455-1162-ND
Conn_Socket_PWR_HDD1,PHR-9,G7_Custom:BOM_ITEM,1,-,PHR-9,Digikey,455-1159-ND
Conn_Socket_BPi_SPLY_atJ5;Conn_Socket_BPi_SPLY1,XHP-2,G7_Custom:BOM_ITEM,2,-,-,Digikey,455-2266-ND
M1,BananaPi_M1,G7_Custom:BananaPi-M1,1,-,-,Digikey, SAM1212-13-ND
J1,12V Power In,G7_Custom:BarrelJack_Wuerth_6941xx301002,1,-,-,Digikey,CP-102A-ND
FL1;FL2,CM2021Y330R-10,G7_Custom:CMC_Laird_CM2021Y330R-10,2,-,-,-,240-2502-1-ND
J5,Molex 0522071860,G7_Custom:Conn_FFC_Molex_52207-1860,1,-,-,-,WM10954CT-ND
J3,DebugAtTiny,G7_Custom:JST_XH_B4B-XH-AM_1x04_P2.50mm_Vertical,1,-,-,Digikey,455-2237-ND
U2,LMZ12003,G7_Custom:LMZ12003_Handsolder,1,-,-,-,LMZ12003TZ-ADJ/NOPBCT-ND 
U4,LTC4359-MS8,G7_Custom:MSOP-8_3x3mm_P0.65mm_Py0.45mm,1, Linear Technology/Analog Devices ,LTC4359CMS8#TRPBF‎ ,Digikey,LTC4359CMS8#TRPBFCT-ND‎
K1,EC2-12TNU,G7_Custom:Relay_Kemet_EC2-12TNU,1,KEMET,EC2-12TNU,Digikey,399-11031-5-ND
PCB1,BaSe_PWR_V3_2,G7_Labels:BaSe_PWR_V3_2,1,-,-,-,-
FB3;FB4;FB5;FB6;FB7;FB10,742792602,Inductor_SMD:L_0603_1608Metric_Pad1.05x0.95mm_HandSolder,6,-,-,Digikey, 732-4660-1-ND
FB2,742792093,Inductor_SMD:L_0805_2012Metric_Pad1.15x1.40mm_HandSolder,1,-,-,Digikey, 732-1609-1-ND
H1;H2;H3;H4,MountingHole,MountingHole:MountingHole_2.2mm_M2,4,-,-,-,-
U5,ATtiny816-S,Package_SO:SOIC-20W_7.5x12.8mm_P1.27mm,1,Microchip Technology,ATTINY816-SFR,Digikey,ATTINY816-SFRCT-ND 
U3,ADG734,Package_SO:TSSOP-20_4.4x6.5mm_P0.65mm,1,-,-,-,ADG734BRUZ-REEL7CT-ND
Q2;Q6;Q7,BSS123,Package_TO_SOT_SMD:SOT-23,3,-,-,-,BSS123LT1GOSCT-ND 
U7,AP2204K-3.3,Package_TO_SOT_SMD:SOT-23-5_HandSoldering,1,-,-,Digikey,AP2204K-3.3TRG1DICT-ND 
U1,INA212,Package_TO_SOT_SMD:SOT-363_SC-70-6_Handsoldering,1, Texas Instruments ,‎INA212AIDCKT‎,Digikey,296-23586-1-ND
Q3,BSC028N06LS3,Package_TO_SOT_SMD:TDSON-8-1,1, Infineon Technologies ,‎BSC028N06NSATMA1‎,Digikey,BSC028N06NSATMA1CT-ND‎
Q4,BSC093N04LS,Package_TO_SOT_SMD:TDSON-8-1,1,-,-,-,BSC093N04LSGATMA1CT-ND
Q1;Q5,BS170,Package_TO_SOT_THT:TO-92_Inline,2,-,-,-,BS170-D75ZCT-ND
R13;R23,0,Resistor_SMD:R_0603_1608Metric_Pad1.05x0.95mm_HandSolder,2,-,-,-,311-47KGRCT-ND 
FB9,0R,Resistor_SMD:R_0603_1608Metric_Pad1.05x0.95mm_HandSolder,1,-,-,-,311-47KGRCT-ND 
Rfbb1,"1,87K",Resistor_SMD:R_0603_1608Metric_Pad1.05x0.95mm_HandSolder,1,-,-,-,P20001CT-ND 
Rfbt1;R5;R19,10k,Resistor_SMD:R_0603_1608Metric_Pad1.05x0.95mm_HandSolder,3,-,-,-,311-10.0KHRCT-ND
R3,1k,Resistor_SMD:R_0603_1608Metric_Pad1.05x0.95mm_HandSolder,1,-,-,-,311-1.00KHRCT-ND
R24;R6;2k4,1k2,Resistor_SMD:R_0603_1608Metric_Pad1.05x0.95mm_HandSolder,3,-,-,-,A129689CT-ND
R8;R11;R10;R9;R12;R2;Ron1;R15;R14;R17;2k3;R20;R4;R16;R25,47k,Resistor_SMD:R_0603_1608Metric_Pad1.05x0.95mm_HandSolder,15,-,-,-,311-47KGRCT-ND 
R7;R22;R21;R18;R26;R27,NO,Resistor_SMD:R_0603_1608Metric_Pad1.05x0.95mm_HandSolder,6,-,-,-,311-47KGRCT-ND 
R1,1m,Resistor_SMD:R_1206_3216Metric_Pad1.42x1.75mm_HandSolder,1,Riedon,CSR1206-0R001F1,Digikey,696-1369-1-ND

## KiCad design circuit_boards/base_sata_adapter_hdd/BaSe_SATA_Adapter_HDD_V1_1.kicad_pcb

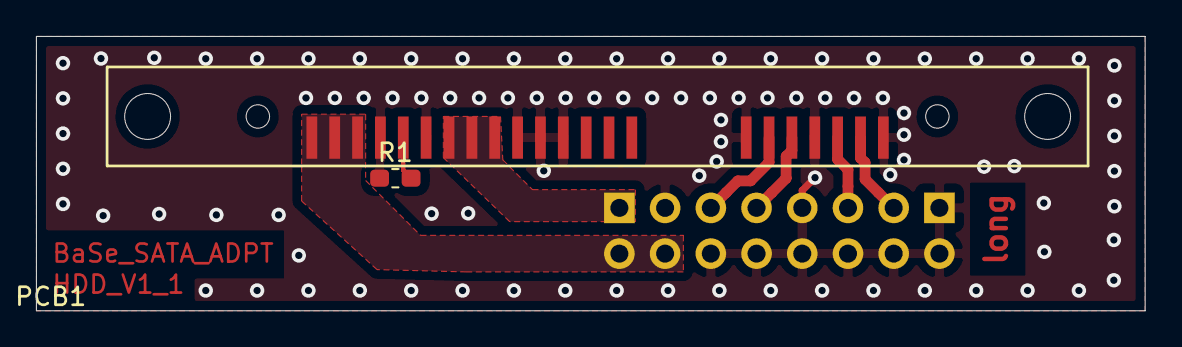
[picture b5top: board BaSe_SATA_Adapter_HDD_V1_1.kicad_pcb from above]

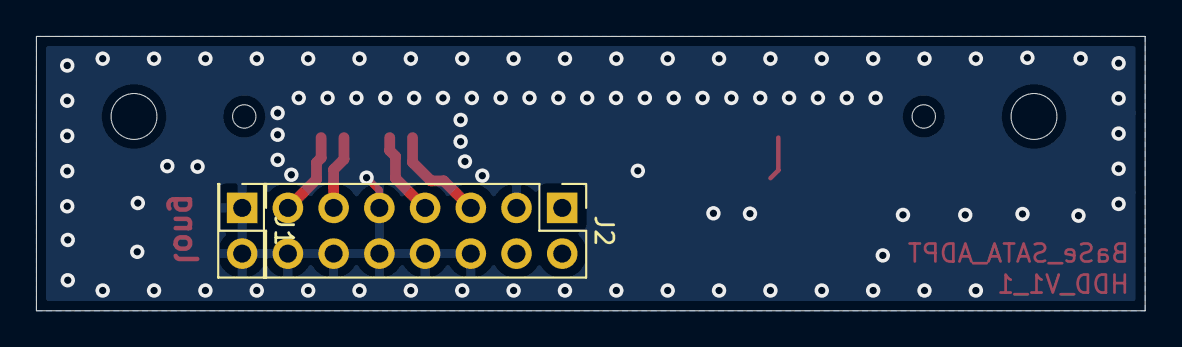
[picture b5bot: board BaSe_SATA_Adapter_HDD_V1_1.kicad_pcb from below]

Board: 2 copper layers, 61.6 x 15.2 mm, 5 parts (2 on the bottom side), 8 nets.

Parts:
J1: 821-22-002-10-004101; Conn_Spring_MaxMill_821-22-002-10-002101
J2: 823-22-014-10-001101; Conn_Spring_MaxMill_823-22-014-10-001101
PCB1: BaSe_SATA_Adapter_HDD_V1_1
R1: No; R_0603_1608Metric_Pad1.05x0.95mm_HandSolder
X1: SATA_CONNECTOR_FEM; Conn_SATA_FEM_3M_5622-2222

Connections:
+5V: J2.1, X1.P7, X1.P8, X1.P9
+12V: J2.2, J2.4, X1.P13, X1.P14, X1.P15
/HDD_Rx+: J2.5, X1.S6
/HDD_Rx-: J2.7, X1.S5
/HDD_Tx+: J2.13, X1.S2
/HDD_Tx-: J2.11, X1.S3
/SPINUP_HDD: R1.2, X1.P11
GND: J1.1, J1.2, J2.3, J2.6, J2.8, J2.9, J2.10, J2.12, J2.14, R1.1, X1.P4, X1.P5, X1.P6, X1.P10, X1.P12, X1.S1, X1.S4, X1.S7

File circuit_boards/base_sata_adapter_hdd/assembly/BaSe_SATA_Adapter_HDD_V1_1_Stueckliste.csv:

Refs,Value,Footprint,Quantity,MFR,MPN,SPR,SPN
X1,SATA_CONNECTOR_FEM,G7_Custom:Conn_SATA_FEM_3M_5622-2222,1,3M,5622-2222-ML,Digikey,3M5557-ND
J1,821-22-002-10-004101,G7_Custom:Conn_Spring_MaxMill_821-22-002-10-002101,1,Mill-Max Manufacturing Corp.,-,Digikey, ED8201-02-ND
J2,823-22-014-10-001101,G7_Custom:Conn_Spring_MaxMill_823-22-014-10-001101,1,Max Mill,-,Digikey, ED8176-14-ND
PCB1,BaSe_SATA_Adapter_HDD_V1_1,G7_Labels:BaSe_SATA_Adapter_HDD_V1_1,1,-,-,-,-
R1,No,Resistor_SMD:R_0603_1608Metric_Pad1.05x0.95mm_HandSolder,1,-,-,-,-

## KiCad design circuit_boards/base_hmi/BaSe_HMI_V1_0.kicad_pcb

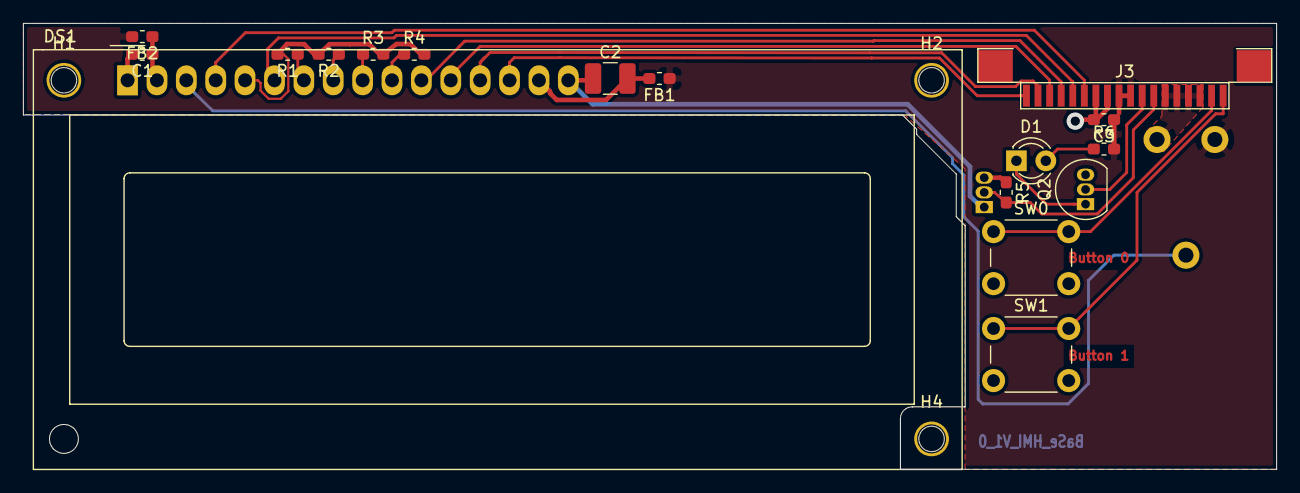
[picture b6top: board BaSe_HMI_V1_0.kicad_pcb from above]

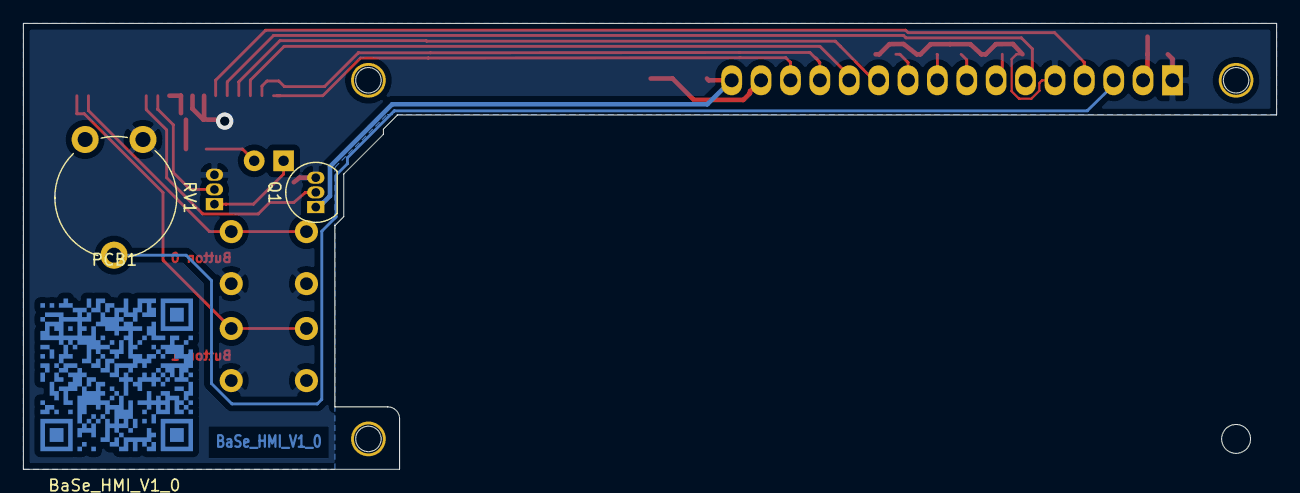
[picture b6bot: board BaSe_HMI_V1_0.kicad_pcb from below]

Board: 2 copper layers, 108.3 x 38.5 mm, 23 parts (3 on the bottom side), 22 nets.

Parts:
C1, C3: 100nF; C_0603_1608Metric_Pad1.05x0.95mm_HandSolder
C2: 100µF; C_1210_3225Metric_Pad1.42x2.65mm_HandSolder
D1: LED; LED_D3.0mm_9.5mm_Standoff
DS1: WC1602A; WC1602A_9.5mm_over_PCB
FB1, FB2: 742792602; L_0603_1608Metric_Pad1.05x0.95mm_HandSolder
H1, H2, H4: MountingHole; MountingHole_2.2mm_M2
J3: 0522071860; Conn_FFC_Molex_52207-1860
PCB1: BaSe_HMI_V1_0
Q1, Q2: BS170; TO-92_Inline
R1, R2, R3, R4, R5: 10k; R_0603_1608Metric_Pad1.05x0.95mm_HandSolder
R6: 1k; R_0603_1608Metric_Pad1.05x0.95mm_HandSolder
RV1: R_POT; Potentiometer_Piher_PT-10-V10_Vertical
SW0, SW1: SW_Push; SW_PUSH_6mm_H7.3mm

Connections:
+5V: C3.1, FB1.1, FB2.2, J3.9, J3.10, R6.2, RV1.1
/Dis_DB4: DS1.11, J3.15
/Dis_DB5: DS1.12, J3.16
/Dis_DB6: DS1.13, J3.17
/Dis_DB7: DS1.14, J3.18
/Dis_E: DS1.6, J3.14
/Dis_PWM: J3.7, Q1.2, R5.2
/Dis_RS: DS1.4, J3.13
/Dis_Vdd: C1.1, DS1.2, FB2.1
/LED+: C2.2, DS1.15, FB1.2
/LED-: C2.1, DS1.16, Q1.1
/LED_HMI: J3.8, Q2.2
/Taster_0: J3.2, SW0.1
/Taster_1: J3.1, SW1.1
GND: C1.2, C3.2, DS1.1, DS1.5, J3.3, J3.4, J3.5, J3.6, J3.11, J3.12, Q1.3, Q2.3, R1.2, R2.2, R3.2, R4.2, R5.1, RV1.3, SW0.2, SW1.2
unnamed: D1.1, Q2.1
unnamed: D1.2, R6.1
unnamed: DS1.3, RV1.2
unnamed: DS1.7, R1.1
unnamed: DS1.8, R2.1
unnamed: DS1.9, R3.1
unnamed: DS1.10, R4.1

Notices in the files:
board/board.h:
ChibiOS - Copyright (C) 2006..2020 Giovanni Di Sirio
Licensed under the Apache License, Version 2.0 (the "License");
